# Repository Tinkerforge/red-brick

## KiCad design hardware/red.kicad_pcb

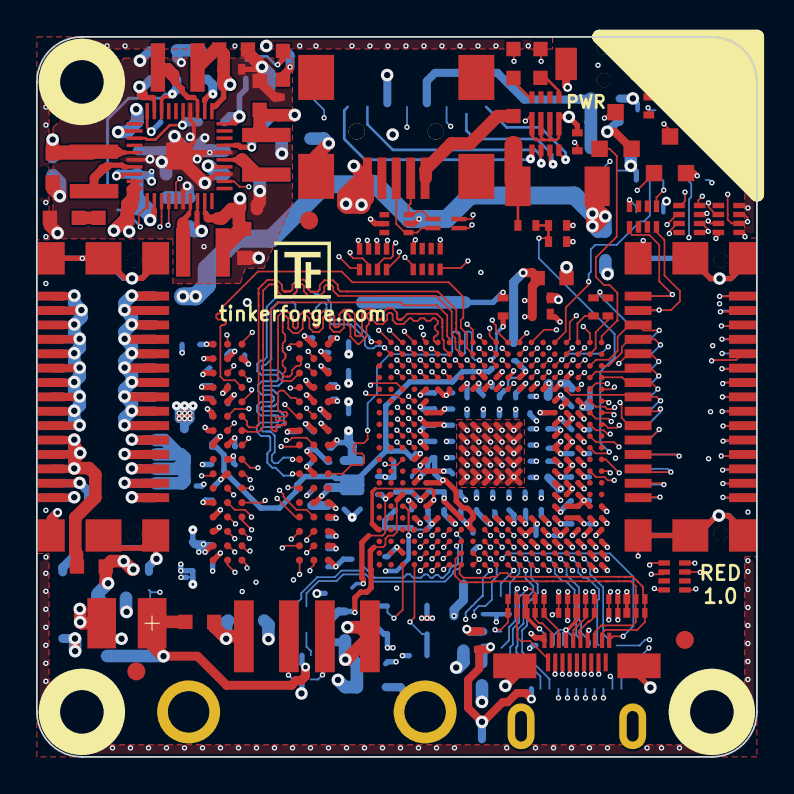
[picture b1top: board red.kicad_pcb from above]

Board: 6 copper layers, 40.0 x 40.0 mm, 188 parts (0 on the bottom side), 204 nets.

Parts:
C1, C2, C4, C5, C6, C7, C8, C9, C10, C11, C13, C16, C17, C18, C19, C20, C21, C22, C23, C24, C27, C28, C29, C31, C32, C34, C35, C36, C37, C38, C39, C40, C41, C42, C43, C44, C45, C46, C47, C49, C50, C51, C52, C53, C54, C55, C57, C59, C68, C69, C70, C71, C72, C73, C79, C80, C81, C86, C87: 220nF; C0402
C3, C15: 9pF; C0402
C12, C33, C74, C92, C97, C98: 22µF/6.3V; C0603
C14, C26, C58, C60, C61, C62, C66, C75, C76, C77, C78, C82, C83, C84, C85, C102: 10µF/6.3V; C0603
C25, C56, C63, C64: 1µF; C0603
C30: 100pF; C0402
C48: 22µF/6.3V; R0603
C65, C67, C93, C94, C101, C103: 100nF; C0402
C88, C89, C90, C91: 1nF; C0402
C95: DNP; C0402
C96: 1µF/6.3V; C0603
C99: 470µF; 3528-21
C100: 100nF; C0805
D1: 1N5819S4; SOD-123
D2: PMEG4050; SOD-128
D3: blue; D0603
D4: green; D0603
D5: red; D0603
D6: B0520LW; SOD-123
F1: 0ZCJ0035FF2G; C1206
FB1, FB2, FB3, FB4, FB5, FB6: FB; C0603
Fiducial_Mark: VAL**; Fiducial_Mark
Fiducial_Mark#2, Fiducial_Mark#3, Fiducial_Mark#4, Fiducial_Mark#5, Fiducial_Mark#6: VAL**; Fiducial_Mark
J1: MICROSDCARD; MicroSD_TF001A
J2: USB-A; USB-A-SMT-8231
J3: MICRO_HDMI; MICRO-HDMI-D
J4: USB-MINI-B-SMD
J5, J7: STACK-UP-LOW; BTB08-ACS-TOP
J6, J8: STACK-DOWN; BTB08-ACS-BTM
L1, L2, L3, L4: 2,2µH; NRH3015
L5: 470nH; C0805
L6, L7: 744230220; WE-CNSW-0603
P1: Camera/EXT; 502078-2110-C
Q1, Q2, Q3: 2N7002; SOT23GDS
R1: 200k; R0402
R2, R4: 1R0; R0402
R3, R7, R8, R27, R29: 1k; R0402
R5, R15: 47k; R0402
R6: 1R0; R0603
R9, R12: 237; R0402
R10, R11: 22; R0402
R13, R14, R19: 10k; R0402
R16, R17: 2k2; R0402
R18: 4.99k; R0402
R20, R21: 0; 4X0402
R22, R23, R24: 22; 4X0402
R25: 0; R0402
R26: DNP; R0402
R28: 100; R0402
RP1: 100k; 4X0402
RP2, RP3: 2k2; 4X0402
RP4: 1k; 4X0402
SW1: Power; TACT-SWITCH
U1: H5TQ4G63AFR; FBGA96
U2: AXP152; QFN40_5X5
U3: RT9701XB; SOT23-5
U4, U8: 82400152; SOT563
U5, U6, U7: TPD4S010DQA
U9: NX3008PBKS; SOT363
U?A1: A10S; TFBGA336
VAL: CE_5mm
VAL#2: WEEE_7mm
X1: 24MHz; CRYSTAL_3225

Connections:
3V3: C2.1, C5.1, C7.1, C9.1, C13.1, C18.1, C20.1, C24.1, C61.2, C82.2, C88.2, D1.1, L1.2, L5.1, P1.2, R3.1, R4.2, R14.1, R27.1, RP1.5, RP1.6, RP1.7, RP1.8, RP2.5, RP2.6, RP2.7, RP2.8, RP4.5, RP4.8, U2.10, U2.39, U9.1, U9.4, U?A1.E5, U?A1.F5, U?A1.G16, U?A1.H16, U?A1.J16, U?A1.K16, U?A1.L16, U?A1.M19, U?A1.M20, U?A1.T14
+1.2V_CPU: C28.1, C32.1, C35.1, C37.1, C39.1, C41.1, C43.1, C45.1, C47.1, C83.2, C89.2, L2.2, U2.7, U?A1.E6, U?A1.E7, U?A1.E8, U?A1.E9, U?A1.E10, U?A1.E11, U?A1.E12, U?A1.E13, U?A1.E14
+1.2V_INT: C27.1, C31.1, C34.1, C36.1, C38.1, C40.1, C42.1, C44.1, C46.1, C85.2, C91.2, L4.2, R2.1, U2.25, U?A1.E15, U?A1.E16, U?A1.F16, U?A1.H4, U?A1.H5, U?A1.M16, U?A1.M17, U?A1.T13, U?A1.U13
+1.5V: C1.1, C4.1, C6.1, C8.1, C11.1, C16.1, C22.1, C48.1, C49.1, C50.1, C51.1, C52.1, C53.1, C54.1, C55.1, C57.1, C59.1, C68.1, C69.1, C70.1, C72.1, C73.1, C74.1, C79.1, C80.1, C81.1, C84.2, C86.1, C87.1, C90.2, C92.1, L3.2, R7.2, U1.A1, U1.A8, U1.B2, U1.C1, U1.C9, U1.D2, U1.D9, U1.E9, U1.F1, U1.G7, U1.H2, U1.H9, U1.K2, U1.K8, U1.N1, U1.N9, U1.R1, U1.R9, U2.11, U?A1.M5, U?A1.N5, U?A1.T5, U?A1.T6, U?A1.T9, U?A1.T10, U?A1.T11
+3.3VP: C60.2, U2.22, U?A1.T15, U?A1.Y17
+5V: C96.1, C101.2, C102.1, D2.2, F1.1, FB6.1, P1.1, R6.2, R16.1, R17.1, U2.29, U2.30, U3.3, U8.5
/DDR/DDR_A0: U1.N3, U?A1.V7
/DDR/DDR_A1: U1.P7, U?A1.R4
/DDR/DDR_A2: U1.P3, U?A1.U8
/DDR/DDR_A3: U1.N2, U?A1.U7
/DDR/DDR_A4: U1.P8, U?A1.P3
/DDR/DDR_A5: U1.P2, U?A1.V8
/DDR/DDR_A6: U1.R8, U?A1.R3
/DDR/DDR_A7: U1.R2, U?A1.V10
/DDR/DDR_A8: U1.T8, U?A1.T3
/DDR/DDR_A9: U1.R3, U?A1.V9
/DDR/DDR_A10: U1.L7, U?A1.M3
/DDR/DDR_A11: U1.R7, U?A1.T4
/DDR/DDR_A12: U1.N7, U?A1.P4
/DDR/DDR_A13: U1.T3, U?A1.U9
/DDR/DDR_A14: U1.T7, U?A1.U3
/DDR/DDR_BA0: U1.M2, U?A1.U6
/DDR/DDR_BA1: U1.N8, U?A1.N3
/DDR/DDR_BA2: U1.M3, U?A1.V6
/DDR/DDR_CLKE: U1.K9, U?A1.L3
/DDR/DDR_D0: U1.E3, U?A1.K1
/DDR/DDR_D1: U1.F7, U?A1.U2
/DDR/DDR_D2: U1.F2, U?A1.J2
/DDR/DDR_D3: U1.F8, U?A1.V1
/DDR/DDR_D4: U1.H3, U?A1.J3
/DDR/DDR_D5: U1.H8, U?A1.W1
/DDR/DDR_D6: U1.G2, U?A1.J1
/DDR/DDR_D7: U1.H7, U?A1.V2
/DDR/DDR_D8: U1.D7, U?A1.T1
/DDR/DDR_D9: U1.C3, U?A1.M1
/DDR/DDR_D10: U1.C8, U?A1.U1
/DDR/DDR_D11: U1.C2, U?A1.K2
/DDR/DDR_D12: U1.A7, U?A1.R2
/DDR/DDR_D13: U1.A2, U?A1.L1
/DDR/DDR_D14: U1.B8, U?A1.T2
/DDR/DDR_D15: U1.A3, U?A1.L2
/DDR/DDR_DQM0: U1.E7, U?A1.P1
/DDR/DDR_DQM1: U1.D3, U?A1.M2
/DDR/DDR_DQS0: U1.F3, U?A1.N1
/DDR/DDR_DQS1: U1.C7, U?A1.P2
/DDR/DDR_NCAS: U1.K3, U?A1.V4
/DDR/DDR_NCS0: U1.L2, U?A1.V5
/DDR/DDR_NDQS0: U1.G3, U?A1.N2
/DDR/DDR_NDQS1: U1.B7, U?A1.R1
/DDR/DDR_NRAS: U1.J3, U?A1.U4
/DDR/DDR_NRST: U1.T2, U?A1.U10
/DDR/DDR_NWE: U1.L3, U?A1.V3
/DDR/DDR_ODT: U1.K1, U?A1.V11
/DDR/_DDR_CLK: R10.1, U?A1.W2
/DDR/_DDR_NCLK: R11.1, U?A1.Y1
/HDMI/USB/_USB_HOST_UDM1: J2.2, U4.3
/HDMI/USB/_USB_HOST_UDP1: J2.3, U4.1
/HDMI/USB/_USB_OTG_UDM0: J4.2, L7.3, U8.6
/HDMI/USB/_USB_OTG_UDP0: J4.3, L7.2, U8.4
CAMERA-I2C-SCL: P1.21, RP2.3, U?A1.J20
CAMERA-I2C-SDA: P1.20, RP2.4, U?A1.J19
DDR_CLK: C95.1, R10.2, U1.J7
DDR_NCLK: C95.2, R11.2, U1.K7
DDR_SVREF: C65.1, C67.1, C70.2, C71.1, C93.1, C94.1, R7.1, R8.2, U1.H1, U1.M8, U?A1.L4, U?A1.U11
GND: C1.2, C2.2, C3.1, C4.2, C5.2, C6.2, C7.2, C8.2, C9.2, C10.2, C11.2, C12.2, C13.2, C14.2, C15.2, C16.2, C17.2, C18.2, C19.2, C20.2, C21.2, C22.2, C23.2, C24.2, C25.1, C26.2, C27.2, C28.2, C29.2, C30.1, C31.2, C32.2, C33.2, C34.2, C35.2, C36.2, C37.2, C38.2, C39.2, C40.2, C41.2, C42.2, C43.2, C44.2, C45.2, C46.2, C47.2, C48.2, C49.2, C50.2, C51.2, C52.2, C53.2, C54.2, C55.2, C56.1, C57.2, C58.1, C59.2, C60.1, C61.1, C62.1, C63.2, C64.2, C65.2, C66.1, C67.2, C68.2, C69.2, C71.2, C72.2, C73.2, C74.2, C75.2, C76.2, C77.2, C78.2, C79.2, C80.2, C81.2, C82.1, C83.1, C84.1, C85.1, C86.2, C87.2, C88.1, C89.1, C90.1, C91.1, C92.2, C93.2, C94.2, C96.2, C97.1, C98.1, C99.2, C100.2, C101.1, C102.2, C103.2, FB2.1, FB4.1, FB5.2, J1.6, J1.S, J2.4, J3.4, J3.7, J3.10, J3.13, J3.16, J3.SHD, J4.5, J5.EP, J6.EP, J7.EP, J8.EP, P1.4, P1.6, P1.8, P1.10, P1.19, Q1.S, Q2.S, Q3.S, R1.1, R8.1, R9.2, R12.2, R13.2, R15.2, R19.1, SW1.1, U1.A9, U1.B1, U1.B3, U1.B9, U1.D1, U1.D8, U1.E1, U1.E2, U1.E8, U1.F9, U1.G1, U1.G8, U1.G9, U1.J2, U1.J8, U1.M1, U1.M9, U1.P1, U1.P9, U1.T1, U1.T9, U2.3, U2.6, U2.14, U2.26, U2.36, U2.EP, U3.2, U4.2, U5.3, U5.8, U6.3, U6.8, U7.3, U7.8, U8.2, U?A1.A6, U?A1.A15, U?A1.A16, U?A1.A17, U?A1.A18, U?A1.A19, U?A1.A20, U?A1.B15, U?A1.B16, U?A1.B17, U?A1.B18, U?A1.B19, U?A1.B20, U?A1.C6, U?A1.C7, U?A1.C8, U?A1.C9, U?A1.C10, U?A1.C11, U?A1.C12, U?A1.C13, U?A1.C14, U?A1.C15, U?A1.C16, U?A1.C17, U?A1.C18, U?A1.D4, U?A1.D6, U?A1.D7, U?A1.D8, U?A1.D9, U?A1.D10, U?A1.D11, U?A1.D12, U?A1.D13, U?A1.D14, U?A1.D15, U?A1.D16, U?A1.D17, U?A1.D18, U?A1.E17, U?A1.E18, U?A1.F17, U?A1.F18, U?A1.G5, U?A1.G17, U?A1.G18, U?A1.H8, U?A1.H9, U?A1.H10, U?A1.H11, U?A1.H12, U?A1.H13, U?A1.H17, U?A1.H18, U?A1.J8, U?A1.J9, U?A1.J10, U?A1.J11, U?A1.J12, U?A1.J13, U?A1.K4, U?A1.K5, U?A1.K8, U?A1.K9, U?A1.K10, U?A1.K11, U?A1.K12, U?A1.K13, U?A1.L5, U?A1.L8, U?A1.L9, U?A1.L10, U?A1.L11, U?A1.L12, U?A1.L13, U?A1.M8, U?A1.M9, U?A1.M10, U?A1.M11, U?A1.M12, U?A1.M13, U?A1.N8, U?A1.N9, U?A1.N10, U?A1.N11, U?A1.N12, U?A1.N13, U?A1.N16, U?A1.P5, U?A1.R5, U?A1.T7, U?A1.T8, U?A1.T12, U?A1.U12, U?A1.U15, U?A1.U16, U?A1.V19, X1.3
HDMI_HCEC: J3.15, U7.1, U7.10, U?A1.R17
HDMI_HHPD: J3.1, R15.1, U7.5, U7.6, U?A1.T17
HDMI_HSCL: J3.17, R16.2, U7.2, U7.9, U?A1.R18
HDMI_HSDA: J3.18, R17.2, U7.4, U7.7, U?A1.T18
HDMI_HTX1N: J3.8, U5.5, U5.6, U?A1.P19
HDMI_HTX1P: J3.6, U5.4, U5.7, U?A1.P20
HDMI_HTX2N: J3.5, U5.2, U5.9, U?A1.N19
HDMI_HTX2P: J3.3, U5.1, U5.10, U?A1.N20
HDMI_HTXCN: J3.14, U6.5, U6.6, U?A1.T19
HDMI_HTXCP: J3.12, U6.4, U6.7, U?A1.T20
HDMI_HTXON: J3.11, U6.2, U6.9, U?A1.R19
HDMI_HTXOP: J3.9, U6.1, U6.10, U?A1.R20
LDO0_OUT: C58.2, C62.2, C75.1, C76.1, C77.1, C78.1, U2.4, U2.12, U2.19, U2.28, U2.32, U2.38
LED_ERROR: Q1.G, U?A1.A1
LED_RUNNING: Q3.G, U?A1.B1
NMI_N: R5.2, U2.31, U?A1.B9
unnamed: C3.2, U?A1.V20, X1.1
unnamed: C10.1, C14.1, R1.2, U?A1.V14
unnamed: C12.1, C17.1, C23.1, R2.2, U?A1.J4, U?A1.J5
unnamed: C15.1, U?A1.U20, X1.2
unnamed: C19.1, C26.1, U?A1.W14
unnamed: C21.1, D1.2, U?A1.P16
unnamed: C25.2, U?A1.V15
unnamed: C29.1, C33.1, R4.1, U?A1.R16
unnamed: C30.2, R29.1, U2.2
unnamed: C56.2, R5.1, U2.18
unnamed: C63.1, U2.20
unnamed: C64.1, U2.15, U2.23
unnamed: C66.2, R6.1
unnamed: C97.2, C98.2, J1.4, L5.2
unnamed: C99.1, FB1.1, U3.1, U3.5, U4.5
unnamed: C100.1, FB1.2, J2.1
unnamed: D2.1, FB3.1, R18.1
unnamed: D3.1, RP4.1
unnamed: D3.2, Q2.D
unnamed: D4.1, R27.2
unnamed: D4.2, Q3.D
unnamed: D5.1, RP4.4
unnamed: D5.2, Q1.D
unnamed: D6.2, J7.28, J8.28
unnamed: F1.2, J3.19
unnamed: FB2.2, J2.SHD
unnamed: FB3.2, J4.1
unnamed: FB4.2, J4.6
unnamed: FB5.1, J7.21, J7.23, J7.25, J7.27, J8.21, J8.23, J8.25, J8.27
unnamed: FB6.2, J7.22, J7.24, J7.26, J8.22, J8.24, J8.26
unnamed: J5.7, J6.7, R28.1
unnamed: J7.1, J7.3, J7.5, J7.7, J7.9, J7.11, J7.13, J7.15, J7.17, J7.19, J8.1, J8.3, J8.5, J8.7, J8.9, J8.11, J8.13, J8.15, J8.17, J8.19
unnamed: J7.2, J7.4, J7.6, J7.8, J7.10, J7.12, J7.14, J7.16, J7.18, J7.20, J8.2, J8.4, J8.6, J8.8, J8.10, J8.12, J8.14, J8.16, J8.18, J8.20
unnamed: J7.29, J8.29
unnamed: J7.30, J8.30
unnamed: L1.1, U2.37
unnamed: L2.1, U2.5
unnamed: L3.1, U2.13
unnamed: L4.1, U2.27
unnamed: L6.1, U4.6
unnamed: L6.4, U4.4
unnamed: P1.3, U?A1.H20
unnamed: P1.5, U?A1.H19
unnamed: P1.7, U?A1.G20
unnamed: P1.9, U?A1.G19
unnamed: P1.11, U?A1.F20
unnamed: P1.12, U?A1.F19
unnamed: P1.13, U?A1.E20
unnamed: P1.14, U?A1.E19
unnamed: P1.15, U?A1.D20
unnamed: P1.16, U?A1.D19
unnamed: P1.17, U?A1.C20
unnamed: P1.18, U?A1.C19
unnamed: R9.1, U?A1.K3
unnamed: R12.1, U1.L8
unnamed: R20.1, U?A1.L18
unnamed: R20.2, U?A1.L17
unnamed: R20.3, U?A1.J18
unnamed: R20.4, U?A1.J17
unnamed: R21.1, U?A1.K17
unnamed: R21.4, U?A1.K18
unnamed: R22.1, U?A1.G2
unnamed: R22.2, U?A1.H1
unnamed: R22.3, U?A1.H2
unnamed: R23.2, U?A1.D1
unnamed: R23.3, U?A1.C3
unnamed: R23.4, U?A1.C2
unnamed: R24.1, U?A1.A5
unnamed: R24.2, U?A1.B6
unnamed: R24.4, U?A1.B7
unnamed: R25.1, U?A1.C1
unnamed: R26.1, U?A1.B2
unnamed: R29.2, SW1.2
unnamed: RP3.5, U9.3
unnamed: RP3.8, U9.6
POWER-I2C-SCK: RP2.1, U2.35, U?A1.L20
POWER-I2C-SDA: RP2.2, U2.34, U?A1.L19
RESET_N: Q2.G, R3.2, U2.33, U?A1.A8
RESET_STACK: R28.2, U?A1.D2
SDCARD_CLK: J1.5, R21.5
SDCARD_CMD: J1.3, R14.2, R21.8
SDCARD_D0: J1.7, R20.7, RP1.2
SDCARD_D1: J1.8, R20.8, RP1.1
SDCARD_D2: J1.1, R20.5, RP1.4
SDCARD_D3: J1.2, R20.6, RP1.3
STACK-EX-0-GP00/JTAG-TDO: J5.19, J6.19, U?A1.F3
STACK-EX-0-GP01/JTAG-TDI: J5.21, J6.21, U?A1.F4
STACK-EX-0-GP02: J5.23, J6.23, U?A1.G3
STACK-EX-1-GP00: J5.25, J6.25, U?A1.A12
STACK-EX-1-GP01: J5.27, J6.27, U?A1.A11
STACK-EX-1-GP02: J5.29, J6.29, U?A1.B12
STACK-HIGH/JTAG-TMS: J5.9, U?A1.E3
STACK-I2C-SCL: J5.4, J6.4, RP3.4, U?A1.A7
STACK-I2C-SDA: J5.2, J6.2, RP3.1, U?A1.B8
STACK-MASTER-DETECT: J6.9, U?A1.G4
STACK-SELECT-00: J5.6, J6.8, U?A1.B3
STACK-SELECT-01: J5.8, J6.10, U?A1.A3
STACK-SELECT-02: J5.10, J6.12, U?A1.C4
STACK-SELECT-03: J5.12, J6.14, U?A1.B4
STACK-SELECT-04: J5.14, J6.16, U?A1.A4
STACK-SELECT-05: J5.16, J6.18, U?A1.D5
STACK-SELECT-06: J5.18, J6.20, U?A1.C5
STACK-SELECT-07: J5.20, U?A1.B5
STACK-SELECT-EX-00: J5.22, J6.22, U?A1.G1
STACK-SELECT-EX-01: J5.24, J6.24, U?A1.H3
STACK-SER2-RTS: J5.30, J6.30, R24.5
STACK-SER2-RXD: J5.26, J6.26, R24.7
STACK-SER2-TXD: J5.28, J6.28, R24.8
STACK-SER-RXD: J5.13, J6.13, R22.6
STACK-SER-SCK: J5.17, J6.17, R22.8
STACK-SER-TXD: J5.15, J6.15, R22.7
STACK-SPI-MISO: J5.1, J6.1, R23.6
STACK-SPI-MOSI: J5.3, J6.3, R23.7
STACK-SPI-SCLK: J5.5, J6.5, R23.5
STACK-SPI-SELECT: J6.6, R25.2, R26.2
STACK-SW-I2C-PULLUPS: U9.2, U9.5, U?A1.E1
STACK-SYNC/JTAG-TCK: J5.11, J6.11, U?A1.E4
USB-HOST-DRV: R13.1, U3.4, U?A1.D3
USB-OTG-DET: C103.1, R18.2, R19.2, U?A1.B10
USB_HOST_UDM1: L6.3, U?A1.N18
USB_HOST_UDP1: L6.2, U?A1.N17
USB_OTG_UDM0: L7.4, U?A1.P18
USB_OTG_UDP0: L7.1, U?A1.P17

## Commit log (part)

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2015-03-16 image: Add disk space requirement hint to readme
2015-03-31 image: Rebuild libsunxi-mali-x11 to remove conflict with libegl1-mesa-drivers
    libegl1-mesa-drivers is installed indirectly by qt5-default. This will
    remove libsunxi-mali-x11 and xserver-xorg-video-sunximali. This in the
    end results in the X server being unable to find the fbturbo driver.
2015-04-13 image: Adding PPP kernel support and wvdial for mobile internet
2015-04-15 image: Add python-reconfigure which is used for hostname changing feature for operations on the file /etc/hosts
2015-05-07 change footprint of usb host connector to one with pegs
2015-05-11 image: Using sakis3g and umtskeeper instead of wvdial
2015-05-13 image: Add umtskeeper for mobile internet
2015-05-14 image: Fix typo
2015-05-22 image: 1. No need to have variables for installing hostapd and wpa supplicant 2. Do not install usb_modeswitch from the repo
2015-05-25 image: Modified make install to avoid reload rules make rule which fails in chroot
2015-05-29 Don't use unreleased API in Python example
2015-06-01 image: Include kernel headers in image
2015-06-02 java: Break long lines in example
2015-06-12 image: Modify default dnsmasq config with new default domain name which suits better in name resolving standards
2015-06-12 image: Essential headers and tools will be pre-installed so that kernel module building is possible on RED-Brick
2015-06-13 image: Use Octave version 3.6.2 in RED-Brick images so that the bindings work with callbacks in Octave
2015-06-15 Fix typo in Python example
2015-06-16 image: Mount sysfs properly
2015-06-19 image: Mark Octave and related packages so they will be excluded form package upgrades
2015-07-09 image: Enable ACL support for ext3 and add libacl1
    Use for redapid's ACL handling.
2015-07-10 image: Adding lsusb lines
2015-07-10 image: Minor fix
2015-07-14 image: Some updates on the GSM modem issues
2015-07-17 image: Patched version of sakis3g to be used with umtskeeper tool to fix GSM modem related problems
2015-07-18 image: Add signing key for official Mono repository
2015-07-19 image: Adding iptables
2015-07-29 image: Add lcl package to pull in lazbuild
2015-07-29 image: Add openHAB signing key
2015-07-30 image: Don't trap on EXIT in make-root-fs.sh
    Because on exit cleanup is called explicitly.
2015-08-03 sync-time: Ensure that /tmp/sync-time exists before watching it
2015-08-07 Adding SMS humidity example program
2015-08-07 image: Enable more HID kernel drivers
2015-08-07 Adding SMS GPS location example
2015-08-07 Adding README.rst
2015-08-10 Fix typo
2015-08-10 Adding documentation of SMS location example program
2015-08-13 image: sakis3g with 10 retries instead of 20 in case network registration problem. This will reduce delay if there is a problem registering with the network.
2015-08-14 image: No need to include ssmtp
2015-08-17 image: Imrpove trap handling
2015-10-14 image: Enable more Bluetooth kernel drivers
2015-11-03 image: Install sunxi mail driver into the correct directory
    Before, the Debian EGL/GLES packages shadowed the sunxi mali driver.
    Rebuild the Debian EGL/GLES packages with symlinks to libMail.so instead
    of the MESA drivers.
2016-01-19 image: Install snmp-mibs-downloader
    To workaround this Debian bug:
    https://bugs.debian.org/cgi-bin/bugreport.cgi?bug=568550#27
2016-01-27 image: Update PEAR package. This was also causing the root filesystem generation process to fail
2016-02-03 put HDMI mounting pads in paste files
2016-02-15 Add changelog date and commit after the fact
2016-04-04 rtc-time: Assume Real-Time Clock Bricklet's date/time is in localtime
    Don't call the date command in UTC mode.
2016-09-20 opengl: Add version-less symlinks to make Java FX find the OpenGL libraries
2017-03-27 image: Mode boot.cmd to kernel directory
2017-03-27 image: Initial mainline transitional changes
2017-04-01 image: Remove output directory before kernel build
2017-04-01 image: Export toolchain path and remove two additional feature libraries as they cause problem related to Debian version
2017-04-04 image: Update device tree and kernel config
2017-04-05 red-brick: Define empty string for local version info
2017-04-06 image: Update kernel configuration
2017-04-06 image: Disable modules
2017-04-07 image: Update device tree
2017-04-08 image: Build the kernel as debian package and install the kernel and headers from the generated .deb packages
2017-04-14 image: Skip file renaming if file exists
2017-04-14 image: Exclude kernel related packages from being updated
2017-06-01 image: Update TC URL. Instead of using the latest release URL use version specific URL
2017-06-09 image: Update RED Brick device tree source
2017-06-09 image: Update U-BOOT boot command script
2017-06-09 image: Add libssl-dev
2017-06-10 image: Fix package name for versioning hold
2017-06-10 image: Symlink of kernel image is managed by the debian package postinst script
2017-06-13 image: Fix PHP feature installation
2017-06-13 image: Update device tree source
2017-06-14 Update changelog
2017-06-19 Basic changes for user-space switch from Debian Jessie to Stretch
2017-06-20 image: Update image version
2017-06-20 image: Disable building hostapd totally to test if Stretch repo provided one works
2017-06-20 image: Build RTL8188EU driver from Git
2017-06-21 image: Get rid of CRC mismatch error from U-Boot
2017-06-21 image: Disable Octave downgrade, fix hostapd and wpa_supplicant build and some code beautification
2017-06-22 image: Potential fix for qemu error "qemu-2.1.2/tcg/tcg.c:1683: tcg fatal error"
    For more info check, https://bugs.debian.org/cgi-bin/bugreport.cgi?bug=769983
2017-06-22 image: Disable hostapd and wpa_supplicant manual build
2017-06-22 image: For hostapd and wpa_supplicant build the patched version of the latest source
    This is required to support the RTL8188EU based USB WiFi in AP mode
2017-06-23 image: Add packages to "mono" and "kernel_development" groups
2017-06-26 image: Enable 802.11N and 802.11AC support
2017-06-26 image: Remove cpufrequtils
2017-06-26 image: Update kernel config
2017-06-28 image: Make rtl871xdrv driver default in hostapd for backward compatibility with older versions of Brick Viewer
2017-06-29 image: Cleanup kernel boot script
2017-06-29 image: Revert previous wrong push
2017-06-30 image: kernel: Optimize the kernel for single core CPU
2017-07-04 image: Install Mono from Debian repo
2017-07-05 image: Fix Nagios and Node.js/NPM installation
2017-07-06 image: Fix Nagios4 setup
2017-07-06 image: Update included nagios.cfg file to include tinkerforge.cfg from objects directory
2017-07-07 Add 3d information (tbc)
2017-07-07 Add 3d information capacitors and resistors (tbc)
2017-07-12 image: Cleanup multistrap config file
2017-07-12 image: Install recompiled version of fbturbo driver and disable apt-daily
2017-07-12 image: While starting X and desktop environment first switch to tty2
2017-07-12 image: Add recompiled version of fbturbo driver
2017-07-12 image: Add file to indicate GPU is enabled initially
2017-07-13 image: Add package for installing the fbturbo driver
2017-07-13 image: Several fixes
    1. Move addition of tf user at the beginning of the process.
    2. Decouple lightdm removal from display driver installation.
    3. Add reboot and shutdown buttons on the panel.
2017-07-13 image: Update touch calibrator icon
2017-07-13 image: Add /etc/skel structure
2017-07-13 image: Add resources for adding reboot and restart panel buttons
2017-07-13 image: Add bluetooth packages
2017-07-14 image: Add packages to get the screensaver that we use
2017-07-14 image: Fix icons for on panel reboot and shutdown buttons
2017-07-14 image: Fix opening uploaded .py program files from the web interface
2017-07-14 image: Fix RED Brick image version
2017-07-14 image: Also disable apt-daily-upgrade service
2017-07-26 image: Changes to adapt Debian 9
    - Change web interface file name
    - Don't use custom USB modeswitch, use from repo
    - Don't install sakis3g and umts keeper
    - Install OpenHAB2 testing version
2017-07-26 image: Make Ripples default screensaver
2017-07-27 Add 3d information (final)
2017-07-27 RED-Brick: Add 3d model (*.FCStd & *.step)
2017-08-17 image: Don't create automatic connections for ethernet interfaces
2017-09-28 image: Add required PHP extension
2017-09-28 image: Fix JavaScript binding problems related to new Node.js and NPM version
2017-10-04 image: Restore default value of USE_LOCAL_PACKAGES
2017-10-05 image: Use apt instead of apt-get
2017-10-10 image: Explicitly stop OpenHAB2 after installation
2017-10-10 image: By default keep screensaver disabled
2017-10-11 image: Remove unused tf-set-resolution binary
2017-10-12 image: Use new elaborated X server configuration as default configuration
2017-11-08 image: Adapt RED Brick web interface for openHAB 2
2017-11-22 image: Use latest QEMU release which doesn't require to be patched. This also fixes Node.js bindings installation issue
2017-11-22 image: Fix Java, Node.js bindings and hostapd installation
2017-11-22 image: Add note about openHAB 2 web interface availability
2017-11-23 fix changelog: Update Brick Viewer version
2017-12-20 image: Add udiskie for USB automount
2017-12-21 image: Cleanup the default config file for hostapd
2017-12-21 image: Add udisks2 package for USB automount
2018-02-27 image: Update kernel config and device tree
2018-03-03 image: Add htop
2018-03-05 image: Update README.rst
2018-03-05 image: Remove unsupported scripts
2018-03-20 image: Check if installed qemu version is high enough. Build qemu if it is not
2018-03-21 image: Use newer toolchain
2018-03-22 image: Install debian keyring packages so that newer multistrap would not fail complaining about unverified keys.
2018-06-12 Unify and cleanup RED Brick bindings test programs
2018-07-23 image: Enable brickd after install
2018-07-25 Add new 3d model
2018-08-28 image: Make sure added OpenHAB related files have proper user and group ownership
2018-09-24 image: Add lua5.3
2019-02-20 image: Add dependencies for PyQt5
2019-03-07 image: Use Docker for the build system
2019-03-29 Port binding tests to industrial dual relay bricklet.
    Also add C# test.
2019-05-28 image: Better rST usage in readme
2019-06-14 Add hardware tester script
2019-07-19 GPS V2
    small improvements
2019-08-08 image: Copy correct file for web interface
2019-08-09 image: Report overall build process time
2019-08-09 image: Add missing build process dependencies
2019-08-09 image: Unify directory recreation logic
2019-08-12 image: Remove .built files when starting new build process
    To avoid using .built markers from a previous run.
2019-08-12 image: Update changelog date
2019-08-12 image: Fix typo in changelog
2019-08-13 tester: Also check for 3G USB stick
2019-11-15 image: Add RTL8821CU driver
2019-11-19 image: Fix UDEV rule
2019-12-03 image: Add commit refs to changelog
2019-12-04 labview: Add read-file example
2019-12-06 delphi: Truncate remote file before writing
2020-01-14 examples: Use python3 input by default.
2020-02-03 labview: Fix wrong comment
2020-02-03 python: Add read/write files examples
2020-02-26 python: Fix Python 2 support in read/write examples
2020-02-26 java: Update "Change UID" comment style
2020-03-11 python: Report errors as exceptions to capture stack trace
2020-03-11 pyrthon: Add remove file example
2022-07-06 Add license files.

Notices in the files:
hardware/red.kicad_pcb:
Licensed under CERN OHL v.1.1
Copyright (©) 2014, B.Nordmeyer
Copyright Tinkerforge GmbH 2014.
This documentation describes Open Hardware and is licensed under the
CERN OHL v. 1.1.
